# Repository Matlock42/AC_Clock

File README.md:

# AC Clock [WIP]  
I wanted to make a simplistic clock that would use 60Hz mains for both power and timing signal. This used to be quite common.

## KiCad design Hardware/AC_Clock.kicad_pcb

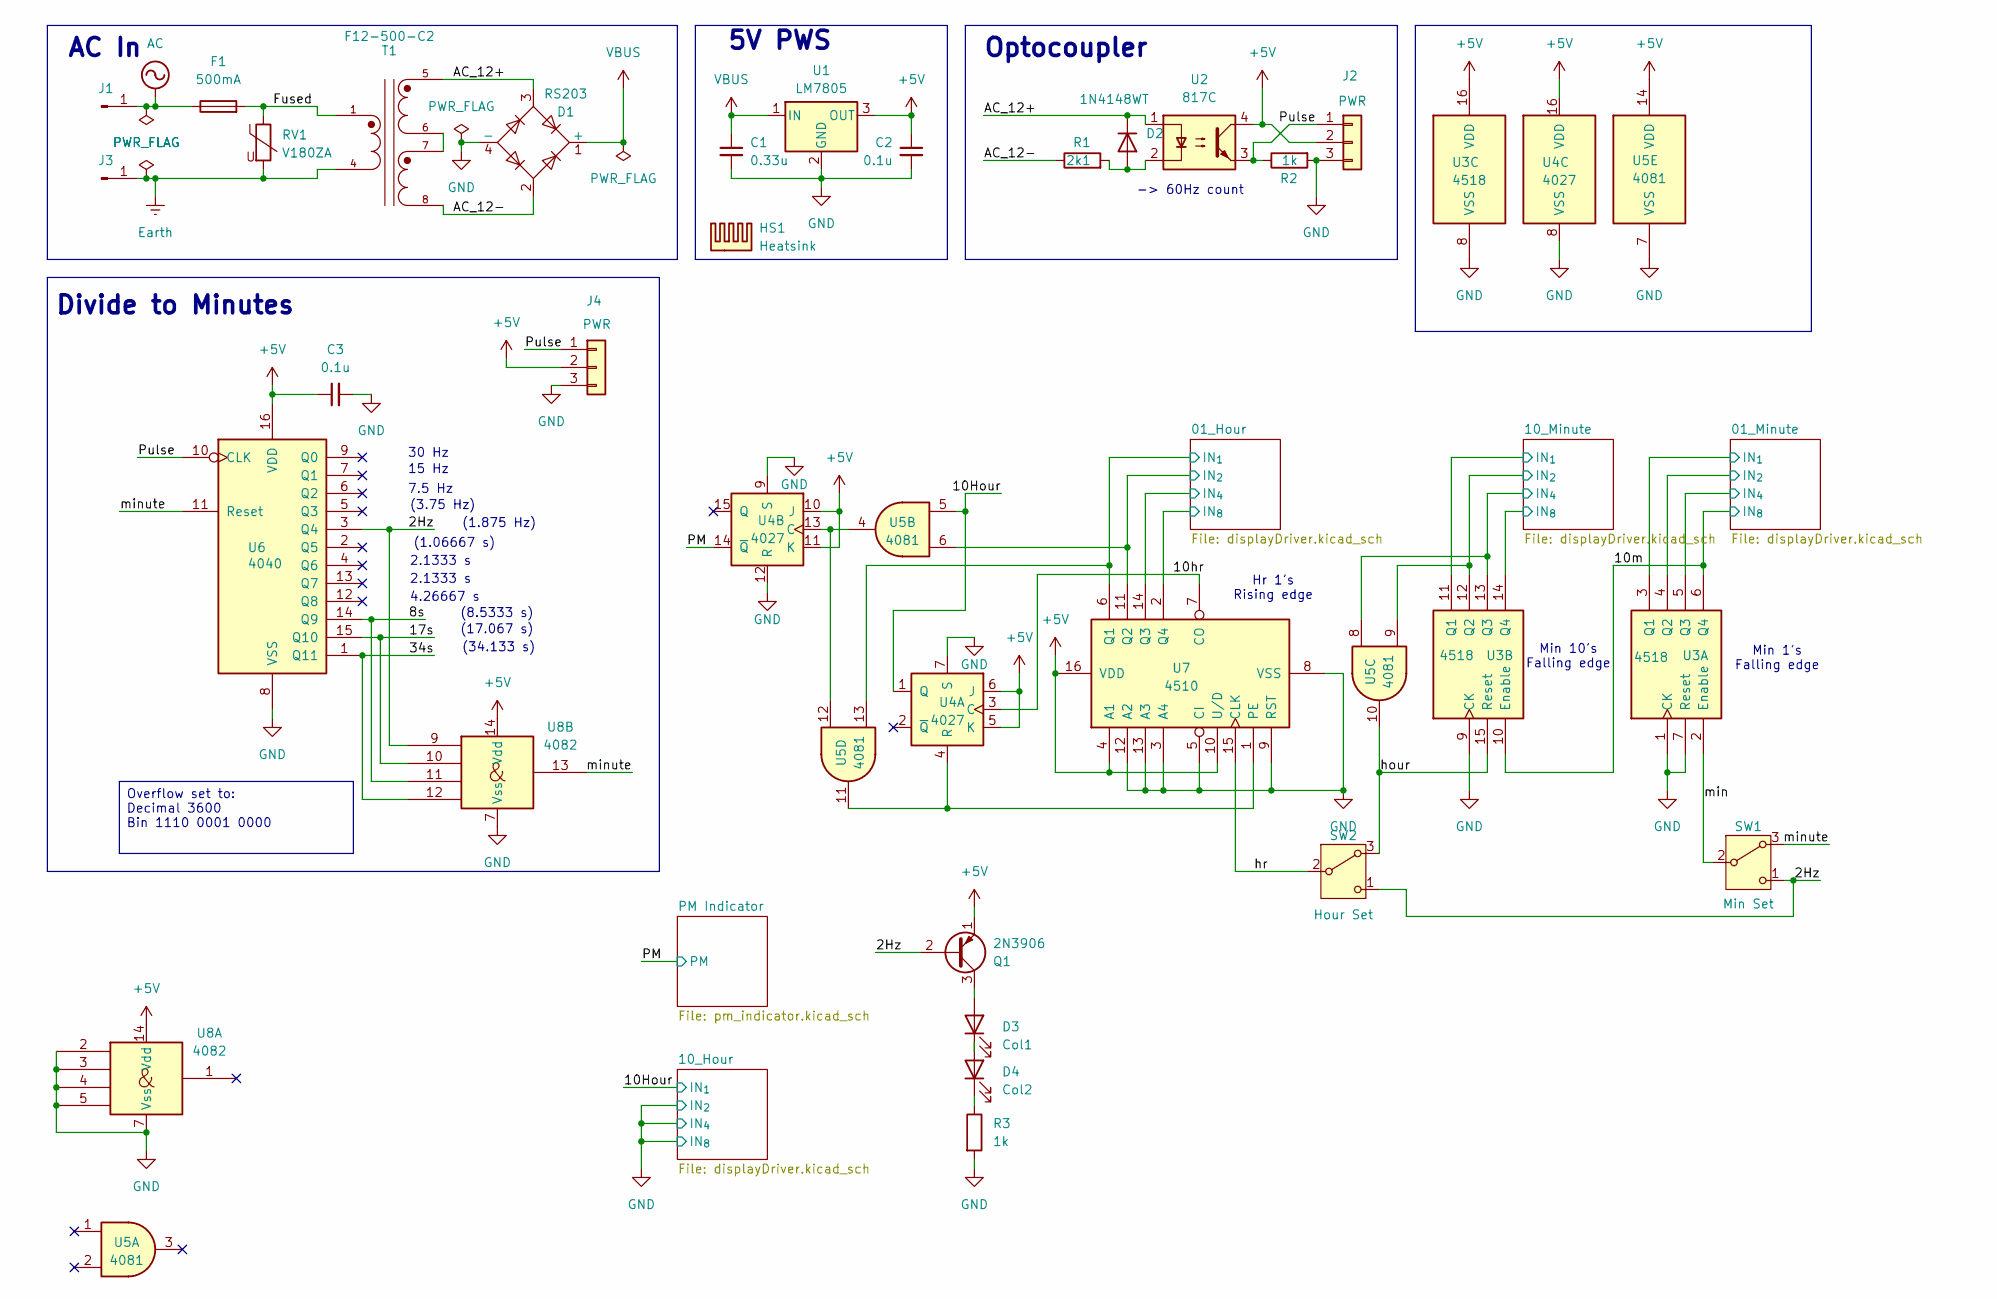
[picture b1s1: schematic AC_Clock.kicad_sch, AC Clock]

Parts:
C1: 0.33u; C_0603_1608Metric
C2, C3: 0.1u; C_0603_1608Metric
D1: RS203; Diode_Bridge_Vishay_KBPM
D2: 1N4148WT; D_SOD-523
D3: Col1; LED_D5.0mm
D4: Col2; LED_D5.0mm
F1: 500mA; Fuse_Littelfuse_372_D8.50mm; MPN MRT 500-BULK
HS1: Heatsink; Heatsink_TO220_CUI_HSS-B20-NP-02
J1: L; Keystone_1287
J2: PWR; PinSocket_1x03_P2.54mm_Vertical
J3: N; Keystone_1287
J4: PWR; PinHeader_1x03_P2.54mm_Vertical
Q1: 2N3906; TO-92_Inline_Wide
R1: 2k1; R_0603_1608Metric
R2, R3: 1k; R_0603_1608Metric
RV1: V180ZA; Varistor_12mm_P7.5mm
SW1: Min Set; SW_Push_CK_PN11SBNA03QE_SPDT_Right_Angle; MPN PN11SBNA03QE
SW2: Hour Set; SW_Push_CK_PN11SBNA03QE_SPDT_Right_Angle; MPN PN11SBNA03QE
T1: F12-500-C2; XFMR_Triad_F12-500-C2
U1: LM7805; TO-220-3_Vertical
U2: 817C; DIP-4_W7.62mm_LongPads
U3: 4518; DIP-16_W7.62mm_Socket_LongPads
U4: 4027; DIP-16_W7.62mm_Socket_LongPads
U5: 4081; DIP-14_W7.62mm_Socket_LongPads
U6: 4040; DIP-16_W7.62mm_Socket_LongPads
U7: 4510; DIP-16_W7.62mm_Socket_LongPads
U8: 4082; DIP-14_W7.62mm_Socket_LongPads

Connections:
+5V: C2.1, C3.1, J2.2, J4.2, Q1.1 (E), U1.3 (OUT), U2.4, U3.16 (VDD), U4.5 (K), U4.6 (J), U4.10 (J), U4.11 (K), U4.16 (VDD), U5.14 (VDD), U6.16 (VDD), U7.4 (A1), U7.10 (U/D), U7.16 (VDD), U8.14 (Vdd); also elsewhere on the board
/01_Hour/IN_{1}: U5.13, U7.6 (Q1); also elsewhere on the board
/01_Hour/IN_{2}: U5.6, U7.11 (Q2); also elsewhere on the board
/01_Hour/IN_{4}: U7.14 (Q3); also elsewhere on the board
/01_Hour/IN_{8}: U7.2 (Q4); also elsewhere on the board
/01_Minute/IN_{1}: U3.3 (Q1); also elsewhere on the board
/01_Minute/IN_{2}: U3.4 (Q2); also elsewhere on the board
/01_Minute/IN_{4}: U3.5 (Q3); also elsewhere on the board
/2Hz: Q1.2 (B), SW1.1 (C), SW2.1 (C), U6.3 (Q4), U8.9
/8s: U6.14 (Q9), U8.11
/10Hour: U4.1 (Q), U5.5; also elsewhere on the board
/10_Minute/IN_{1}: U3.11 (Q1); also elsewhere on the board
/10_Minute/IN_{2}: U3.12 (Q2), U5.9; also elsewhere on the board
/10_Minute/IN_{4}: U3.13 (Q3), U5.8; also elsewhere on the board
/10_Minute/IN_{8}: U3.14 (Q4); also elsewhere on the board
/10hr: U4.3 (C), U7.7 (CO)
/10m: U3.6 (Q4), U3.10 (Enable); also elsewhere on the board
/17s: U6.15 (Q10), U8.10
/34s: U6.1 (Q11), U8.12
/AC_12+: D1.3, D2.1 (K), T1.5, U2.1
/AC_12-: D1.2, R1.1, T1.8
/Fused: F1.2, RV1.1, T1.1
/PM: U4.14 (~Q); also elsewhere on the board
/Pulse: J2.1, J4.1, R2.1, U2.3, U6.10 (CLK)
/hour: SW2.3 (A), U3.15 (Reset), U5.10
/hr: SW2.2 (B), U7.15 (CLK)
/min: SW1.2 (B), U3.2 (Enable)
/minute: SW1.3 (A), U6.11 (Reset), U8.13
AC: F1.1, J1.1
Earth: J3.1, RV1.2, T1.4
GND: C1.2, C2.2, C3.2, D1.4 (-), J2.3, J4.3, R2.2, R3.2, U1.2 (GND), U3.1 (CK), U3.7 (Reset), U3.8 (VSS), U3.9 (CK), U4.7 (S), U4.8 (VSS), U4.9 (S), U4.12 (R), U5.7 (VSS), U6.8 (VSS), U7.3 (A4), U7.5 (CI), U7.8 (VSS), U7.9 (RST), U7.12 (A2), U7.13 (A3), U8.2, U8.3, U8.4, U8.5, U8.7 (Vss); also elsewhere on the board
unnamed: D2.2 (A), R1.2, U2.2
unnamed: D3.2 (A), Q1.3 (C)
unnamed: D3.1 (K), D4.2 (A)
unnamed: D4.1 (K), R3.1
unnamed: T1.6, T1.7
unnamed: U4.4 (R), U5.11, U7.1 (PE)
unnamed: U4.13 (C), U5.4, U5.12
VBUS: C1.1, D1.1 (+), U1.1 (IN)

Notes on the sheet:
-> 60Hz count
30 Hz
(34.133 s)
(17.067 s)
(1.875 Hz)
(3.75 Hz)
15 Hz
Optocoupler
5V PWS
(8.5333 s)
2.1333 s
7.5 Hz
4.26667 s
Divide to Minutes
(1.06667 s)
Min 10's Falling edge
AC In
Min 1's Falling edge
Hr 1's Rising edge
Overflow set to: Decimal 3600 Bin 1110 0001 0000

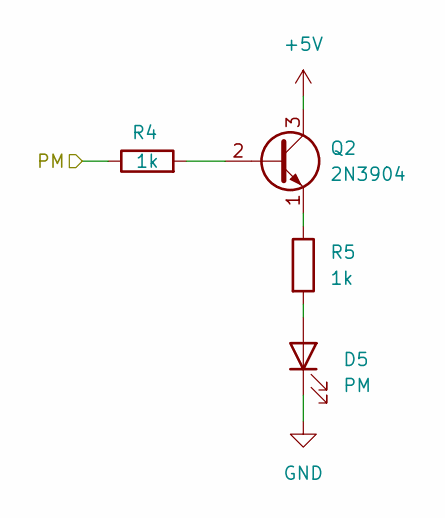
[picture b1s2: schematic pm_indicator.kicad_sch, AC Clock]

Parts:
D5: PM; LED_D5.0mm
Q2: 2N3904; TO-92_Inline_Wide
R4, R5: 1k; R_0603_1608Metric

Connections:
+5V: Q2.3 (C); also elsewhere on the board
/PM: R4.1; also elsewhere on the board
GND: D5.1 (K); also elsewhere on the board
unnamed: D5.2 (A), R5.2
unnamed: Q2.2 (B), R4.2
unnamed: Q2.1 (E), R5.1

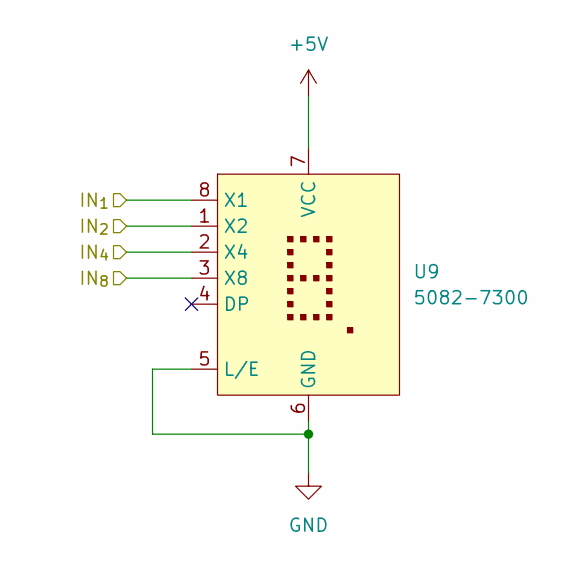
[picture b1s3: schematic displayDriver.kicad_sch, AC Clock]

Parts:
U9: 5082-7300; Display_HP_5082-7300

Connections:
+5V: U9.7 (VCC); also elsewhere on the board
/01_Minute/IN_{1}: U9.8 (X1); also elsewhere on the board
/01_Minute/IN_{2}: U9.1 (X2); also elsewhere on the board
/01_Minute/IN_{4}: U9.2 (X4); also elsewhere on the board
/10m: U9.3 (X8); also elsewhere on the board
GND: U9.5 (L/E), U9.6 (GND); also elsewhere on the board

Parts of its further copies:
U10, U11, U12: 5082-7300; Display_HP_5082-7300

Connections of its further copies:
+5V: U10.7 (VCC), U11.7 (VCC), U12.7 (VCC); also elsewhere on the board
/01_Hour/IN_{1}: U11.8 (X1); also elsewhere on the board
/01_Hour/IN_{2}: U11.1 (X2); also elsewhere on the board
/01_Hour/IN_{4}: U11.2 (X4); also elsewhere on the board
/01_Hour/IN_{8}: U11.3 (X8); also elsewhere on the board
/10Hour: U12.8 (X1); also elsewhere on the board
/10_Minute/IN_{1}: U10.8 (X1); also elsewhere on the board
/10_Minute/IN_{2}: U10.1 (X2); also elsewhere on the board
/10_Minute/IN_{4}: U10.2 (X4); also elsewhere on the board
/10_Minute/IN_{8}: U10.3 (X8); also elsewhere on the board
GND: U10.5 (L/E), U10.6 (GND), U11.5 (L/E), U11.6 (GND), U12.1 (X2), U12.2 (X4), U12.3 (X8), U12.5 (L/E), U12.6 (GND); also elsewhere on the board

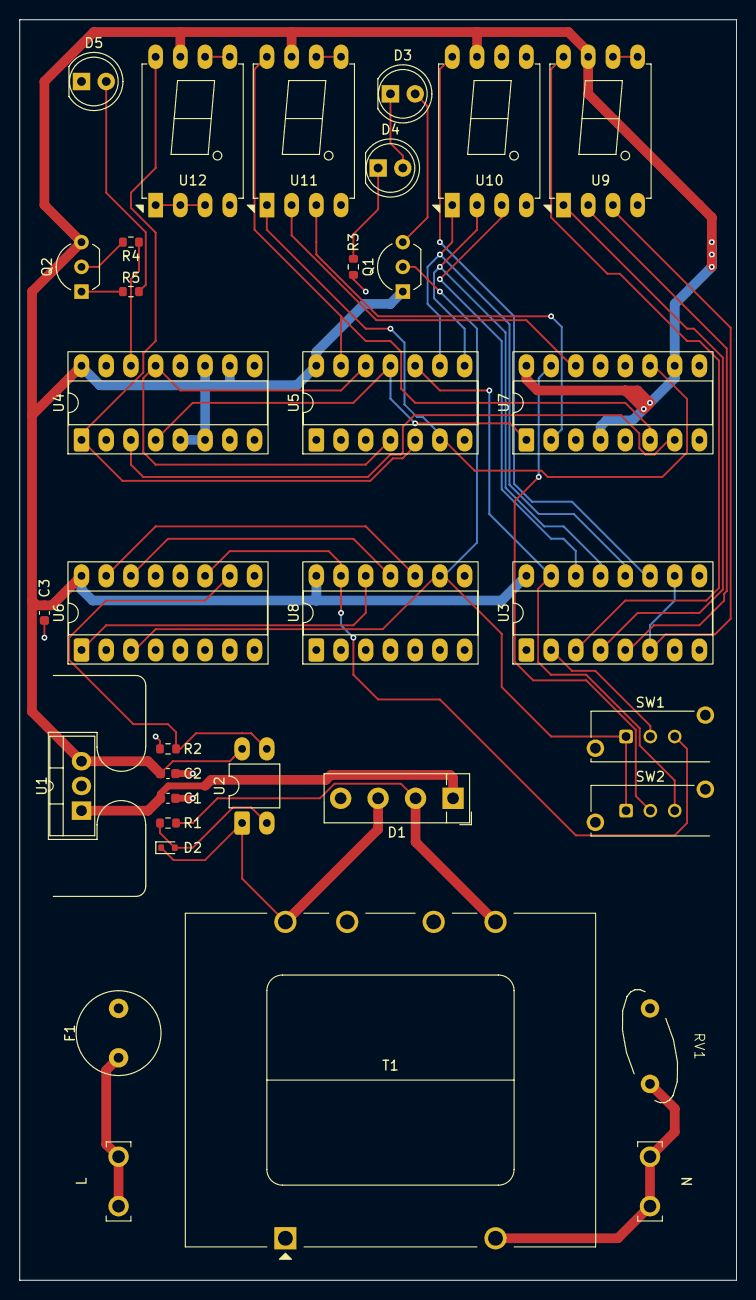
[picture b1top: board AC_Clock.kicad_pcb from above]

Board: 2 copper layers, 73.7 x 129.5 mm, 35 parts (0 on the bottom side), 42 nets.

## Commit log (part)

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2024-06-26 Initalize Blank project
2024-06-26 Add Power circuits and pulse input
2024-06-26 Add frequency divider (60Hz to min) and minutes counter
2024-06-26 Add current calculations
2024-06-26 Add in BCD net-labels and clean up drawings.
2024-06-26 Add Hour Counter and display driver for minutes and ten minutes
2024-06-26 Add in hours and 10-hour display driver
2024-06-26 Add pushbuttons to be able to set time
2024-06-26 Set Footprints for components
2024-06-26 Work on routing
2024-06-26 Add in correct calculated times for frequency divider
2024-06-26 Fix the counters' reset signals
2024-06-28 Add in connectors for display board interconnect
2024-06-28 Adjust minutes resistor packs to make them flow better
2024-07-02 Wire up the 10/Minutes display
2024-07-02 Wire up the Hours connectors
2024-07-02 Fix resistor arrays for more logical layout
2024-07-02 Route the 10/hours digits. Update HDSP-816E footprint to include 3D representation
2024-07-02 Finish routing main board
2024-07-03 Fix 12-bit counter overflow
2024-07-08 Add Class Y Safety capacitor
2024-07-08 Fix U2 footprint; change to DIP-4
2024-07-09 Fix routing and clean up silkscreen
2024-07-10 Found some reference designs because counting is hard
2024-07-10 Add some notes on what ICs to change and switch Safety Capacitor to Y1 type
2024-07-12 Make the IC changes for minute and hour counters
2024-07-12 Remove old ICs
2024-07-16 Change transformers and clean up some wiring
2024-07-17 Clean up wiring and add comments
2024-07-24 Update component symbols and footpints
2024-07-24 Convert layout to 3 board design (power/logic/display)
2024-07-26 Route traces on new layout
2024-07-27 Change copper pour to clearance of 0.25mm
2024-07-30 Update board layout to minimize space used
2024-07-30 Move Power board layout to clear the Pushbuttons Add keepout.
2024-08-09 Change to fuse of correct value
